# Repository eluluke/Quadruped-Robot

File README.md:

# Quadruped Robot

Open-source, 3D-printable, modular quadruped robot designed as a hardware platform for robotics education, controls development, kinematics, reinforcement learning, robotic vision, and future semi-commercial research applications.

This project focuses on building a practical legged robot platform using custom cycloidal actuators, off-the-shelf electronics, CAN-based motor communication, and open-source low-level motor control software. The goal is to create a robot that is mechanically capable, reproducible, and flexible enough for future work in locomotion, autonomous navigation, and robotics research.

## Project Overview

The quadruped is a 12-degree-of-freedom robotic platform with three actuated joints per leg. The mechanical design uses custom 3D-printed cycloidal actuators with a 17:1 gear ratio. These actuators were designed to make the robot modular, serviceable, and easier to manufacture using accessible tools such as 3D printers.

The CAD design is complete, and the actuator assemblies have been built. The current electronics setup uses off-the-shelf hardware for development and testing, while the repository also includes ongoing custom FOC driver board design files. Software development is focused on low-level actuator communication, calibration, inverse kinematics, single-leg testing, and full quadruped locomotion.

Full walking is still under development.

## Current Status

| Area                          | Status                                                   |
| ----------------------------- | -------------------------------------------------------- |
| CAD design                    | Complete                                                 |
| Actuator design               | Complete                                                 |
| Actuator build                | Complete                                                 |
| Electronics                   | Off-the-shelf electronics currently used for development |
| Custom FOC board              | KiCad design files included / in development             |
| Low-level motor communication | Based on Berkeley Humanoid Lite low-level code           |
| Calibration scripts           | In progress                                              |
| Single-leg control            | In progress                                              |
| Full quadruped walking        | In development                                           |
| Vision/autonomy               | Future work                                              |

## Features

* 12-DOF quadruped layout
* Three actuators per leg
* Custom 17:1 cycloidal actuator design
* 3D-printable mechanical structure
* Modular leg and actuator design
* CAD files for the full robot body, legs, and accessories
* CAN-based actuator communication
* Low-level motor control using Berkeley Humanoid Lite/Recoil-style communication code
* Calibration scripts for actuator setup and configuration
* Forward and inverse kinematics tools
* Early locomotion and gait-control scripts
* Xbox controller testing scripts for manual actuator/robot control
* KiCad files for custom FOC driver board development
* BOM and purchasing documentation

## Repository Structure

```text
Quadruped-Robot/
├── 3D_Model/
│   ├── Accessory/
│   ├── Quadruped Body/
│   └── Quadruped Leg/
│
├── Control_Code/
│   ├── Calibration/
│   ├── Locomotion/
│   ├── lowlevel_actuator/
│   ├── quad_ik_can/
│   └── recoil/
│
├── Documentation/
│
├── KiCAD Files/
│   ├── 3D models/
│   ├── BHL_S1_Current/
│   ├── Footprints/
│   ├── Protoype1_Final_revision/
│   └── Symbols/
│
├── Motor_Firmware/
│
├── Purchasing/
│   ├── BOM/
│   └── RFF/
│
└── README.md
```
CAD files are maintained separately at:
https://github.com/eluluke/Quadruped_Robot_Moo_CAD
## Folder Descriptions

### `3D_Model/`

Contains the mechanical design files for the robot. This includes accessory parts, the quadruped body assembly, and leg assembly files.

Important areas include:

* `Accessory/` — printable accessory parts such as body covers and handles
* `Quadruped Body/` — full robot body assembly files
* `Quadruped Leg/` — leg assembly files

These files are used for manufacturing, assembly planning, and future mechanical revisions.

### `Control_Code/`

Contains the Python control software for actuator testing, calibration, kinematics, and early locomotion development.

#### `Control_Code/Calibration/`

Scripts used for setting up and validating individual actuators and motor controllers.

Examples include:

* `ping.py` — basic communication test
* `calibrate_electrical_offset.py` — motor/encoder electrical offset calibration
* `configure_parameter.py` — motor controller parameter configuration
* `read_configurations.py` — read back motor controller settings
* `move_actuator.py` — basic actuator motion test

#### `Control_Code/Locomotion/`

Main area for robot-level locomotion development.

Includes:

* Forward kinematics
* Inverse kinematics
* Leg configuration
* Gain configuration
* Gait scheduling
* Robot controller scripts
* Xbox controller configuration
* IMU reading utilities
* Single-leg and quadruped testing scripts

Notable files include:

* `quadruped_leg_fk.py`
* `quadruped_leg_ik.py`
* `leg_controller.py`
* `robot_controller.py`
* `gait_scheduler.py`
* `quadruped_main_slim.py`
* `quadruped_main_state.py`
* `single_leg_trot.py`
* `remote_single_leg_trot.py`
* `xbox_home_v5.py`
* `read_bno055_live.py`

#### `Control_Code/lowlevel_actuator/`

Contains lower-level actuator test scripts used to command one or more actuators directly.

Examples include:

* `actuator_move_position.py`
* `actuator_ramp_position.py`
* `actuator_ramp_rel_pos.py`
* `triple_actuator_homing.py`
* `triple_actuator_rel_pos.py`
* `xbox_position_control_test.py`
* `xbox_velocity_control_test.py`

These scripts are useful for validating actuator behavior before integrating the full robot.

#### `Control_Code/quad_ik_can/`

Contains an additional inverse-kinematics-over-CAN control workflow.

Includes:

* `can_interface.py`
* `config.py`
* `ik_solver.py`
* `main.py`
* `README.md`

This section appears to be focused on combining inverse kinematics commands with CAN communication.

#### `Control_Code/recoil/`

Contains the low-level Recoil-style communication code used to interface with the FOC motor drivers.

This project uses the Berkeley Humanoid Lite low-level code as the foundation for communicating with the FOC drivers.

Files include:

* `can.py`
* `core.py`
* `fixed16.py`
* `util.py`

## Mechanical Design

The robot is built around custom cycloidal actuators. Each actuator is designed to be compact, modular, and manufacturable with accessible tools. The use of a cycloidal gearbox provides a high reduction ratio while keeping the actuator package suitable for legged robotics.

The mechanical system was designed with the following goals:

* Keep the robot modular and easy to repair
* Make the actuator design reproducible
* Use 3D printing where practical
* Reduce complexity compared to fully custom machined systems
* Provide enough torque and structure for walking development
* Create a platform that can support future controls and autonomy work

## Electronics

The current robot uses off-the-shelf electronics for development and testing. This makes it easier to focus on actuator validation, CAN communication, calibration, and walking control before depending on fully custom hardware.

The repository also includes KiCad files for custom FOC driver board development. These files include PCB designs, schematics, footprints, symbols, 3D models, and previous design revisions.

### `KiCAD Files/`

This folder contains custom motor controller PCB design files and related KiCad resources.

Included resources:

* KiCad project files
* PCB layout files
* Schematic files
* Footprints
* Symbols
* 3D models
* Older board revisions
* Prototype revisions

This section is useful for future development of custom motor-control electronics.

### `Motor_Firmware/`

Contains motor firmware resources, including a modified Recoil motor controller firmware archive.

## Software

The control software is written primarily in Python and is organized around actuator bring-up, calibration, inverse kinematics, and locomotion development.

The current low-level communication approach is based on the Berkeley Humanoid Lite low-level code. This code is used to communicate with the FOC drivers and send actuator commands over CAN.

### Software Goals

* Establish reliable communication with each actuator
* Test individual motor and actuator behavior
* Validate actuator direction, encoder feedback, and control modes
* Calibrate electrical offsets and controller parameters
* Develop single-leg control
* Develop inverse kinematics for each leg
* Build toward coordinated full-body locomotion
* Eventually support higher-level walking, autonomy, and vision experiments

## Running and Testing

Example test scripts are available in the Berkeley Humanoid Lite low-level software and in this repository’s `Control_Code/` folder.

A typical development workflow is:

1. Set up the Python environment.
2. Connect the CAN interface and motor controller hardware.
3. Confirm communication with the actuator.
4. Run a basic ping or configuration read test.
5. Calibrate the actuator electrical offset.
6. Test basic actuator movement.
7. Test multiple actuators together.
8. Run inverse kinematics tests.
9. Test single-leg motion.
10. Move toward full quadruped locomotion.

Example scripts to start with:

```bash
python Control_Code/Calibration/ping.py
python Control_Code/Calibration/read_configurations.py
python Control_Code/Calibration/calibrate_electrical_offset.py
python Control_Code/Calibration/move_actuator.py
```

For low-level actuator tests:

```bash
python Control_Code/lowlevel_actuator/actuator_move_position.py
python Control_Code/lowlevel_actuator/actuator_ramp_position.py
python Control_Code/lowlevel_actuator/triple_actuator_homing.py
```

For locomotion and kinematics development:

```bash
python Control_Code/Locomotion/ik_terminal_test.py
python Control_Code/Locomotion/single_leg_trot.py
python Control_Code/Locomotion/quadruped_main_slim.py
python Control_Code/Locomotion/quadruped_main_state.py
```

Exact commands may need to be adjusted depending on the CAN interface, operating system, motor IDs, and hardware configuration.

## Development Notes

This project is still actively being developed. Many scripts are experimental and may need to be updated for a specific hardware setup.

Before running full robot tests, verify:

* CAN interface name and bitrate
* Motor controller IDs
* Encoder direction
* Motor phase order
* Joint limits
* Homing offsets
* Control gains
* Power supply current limit
* Emergency stop or disconnect method

## Safety Notes

This project involves motors, gear reductions, motor controllers, power electronics, and moving robotic limbs. Use caution when testing.

Recommended safety practices:

* Test actuators one at a time before full robot integration
* Keep the robot lifted or supported during early walking tests
* Use current limits during initial motor testing
* Keep hands, wires, and tools away from moving joints
* Have an emergency stop or quick power disconnect available
* Double-check wiring before applying power
* Verify motor direction before installing actuators into the full robot
* Confirm joint limits before running autonomous motion
* Avoid testing high-power motion near people or fragile objects
* Monitor motor and driver temperature during testing
* Do not leave powered actuators unattended

This robot is still under development, so all testing should be done carefully and incrementally.

## Documentation

The `Documentation/` folder contains project images and supporting documents. More build documentation, assembly instructions, wiring diagrams, CAD renders, and videos will be added as the project progresses.

## Purchasing and BOM

The `Purchasing/` folder contains bill of materials files, expense tracking, and request-for-funding documentation.

This includes:

* FOC drive board BOM
* Overall robot BOM
* Expense tracker
* Funding/request documentation

These files are useful for tracking cost, sourcing parts, and documenting project funding.

## Roadmap

### Completed

* Designed the full quadruped CAD model
* Designed custom cycloidal actuators
* Built the actuator assemblies
* Created 3D-printable body, leg, and accessory files
* Set up off-the-shelf electronics for development
* Added low-level actuator testing scripts
* Added calibration scripts
* Added forward and inverse kinematics code
* Added early locomotion and single-leg test scripts
* Added KiCad files for custom FOC driver board development

### In Progress

* Low-level actuator testing
* Motor communication and control validation
* Actuator calibration
* Leg-level control development
* Gait scheduling
* Single-leg trot testing
* Full quadruped walking development

### Future Work

* Full quadruped walking demo
* Improved gait generation
* Higher-level body control
* Autonomous navigation
* Robotic vision integration
* Custom electronics refinement
* Cleaner software setup instructions
* Assembly guide
* Wiring diagrams
* CAD renders and demo videos
* More complete documentation for calibration and testing

## Acknowledgments

This project uses the Berkeley Humanoid Lite low-level code as the foundation for communication with the FOC drivers.

The project is inspired by open-source robotics platforms and the goal of making advanced legged robotics more accessible for students, researchers, and builders.

## Project Status Disclaimer

This repository is still a work in progress. The CAD and actuator builds are complete, but full walking control is still under development. Some scripts are experimental and may require hardware-specific configuration before use.

## License

License information has not been finalized yet. Add the appropriate license before using this project for public distribution or commercial work.

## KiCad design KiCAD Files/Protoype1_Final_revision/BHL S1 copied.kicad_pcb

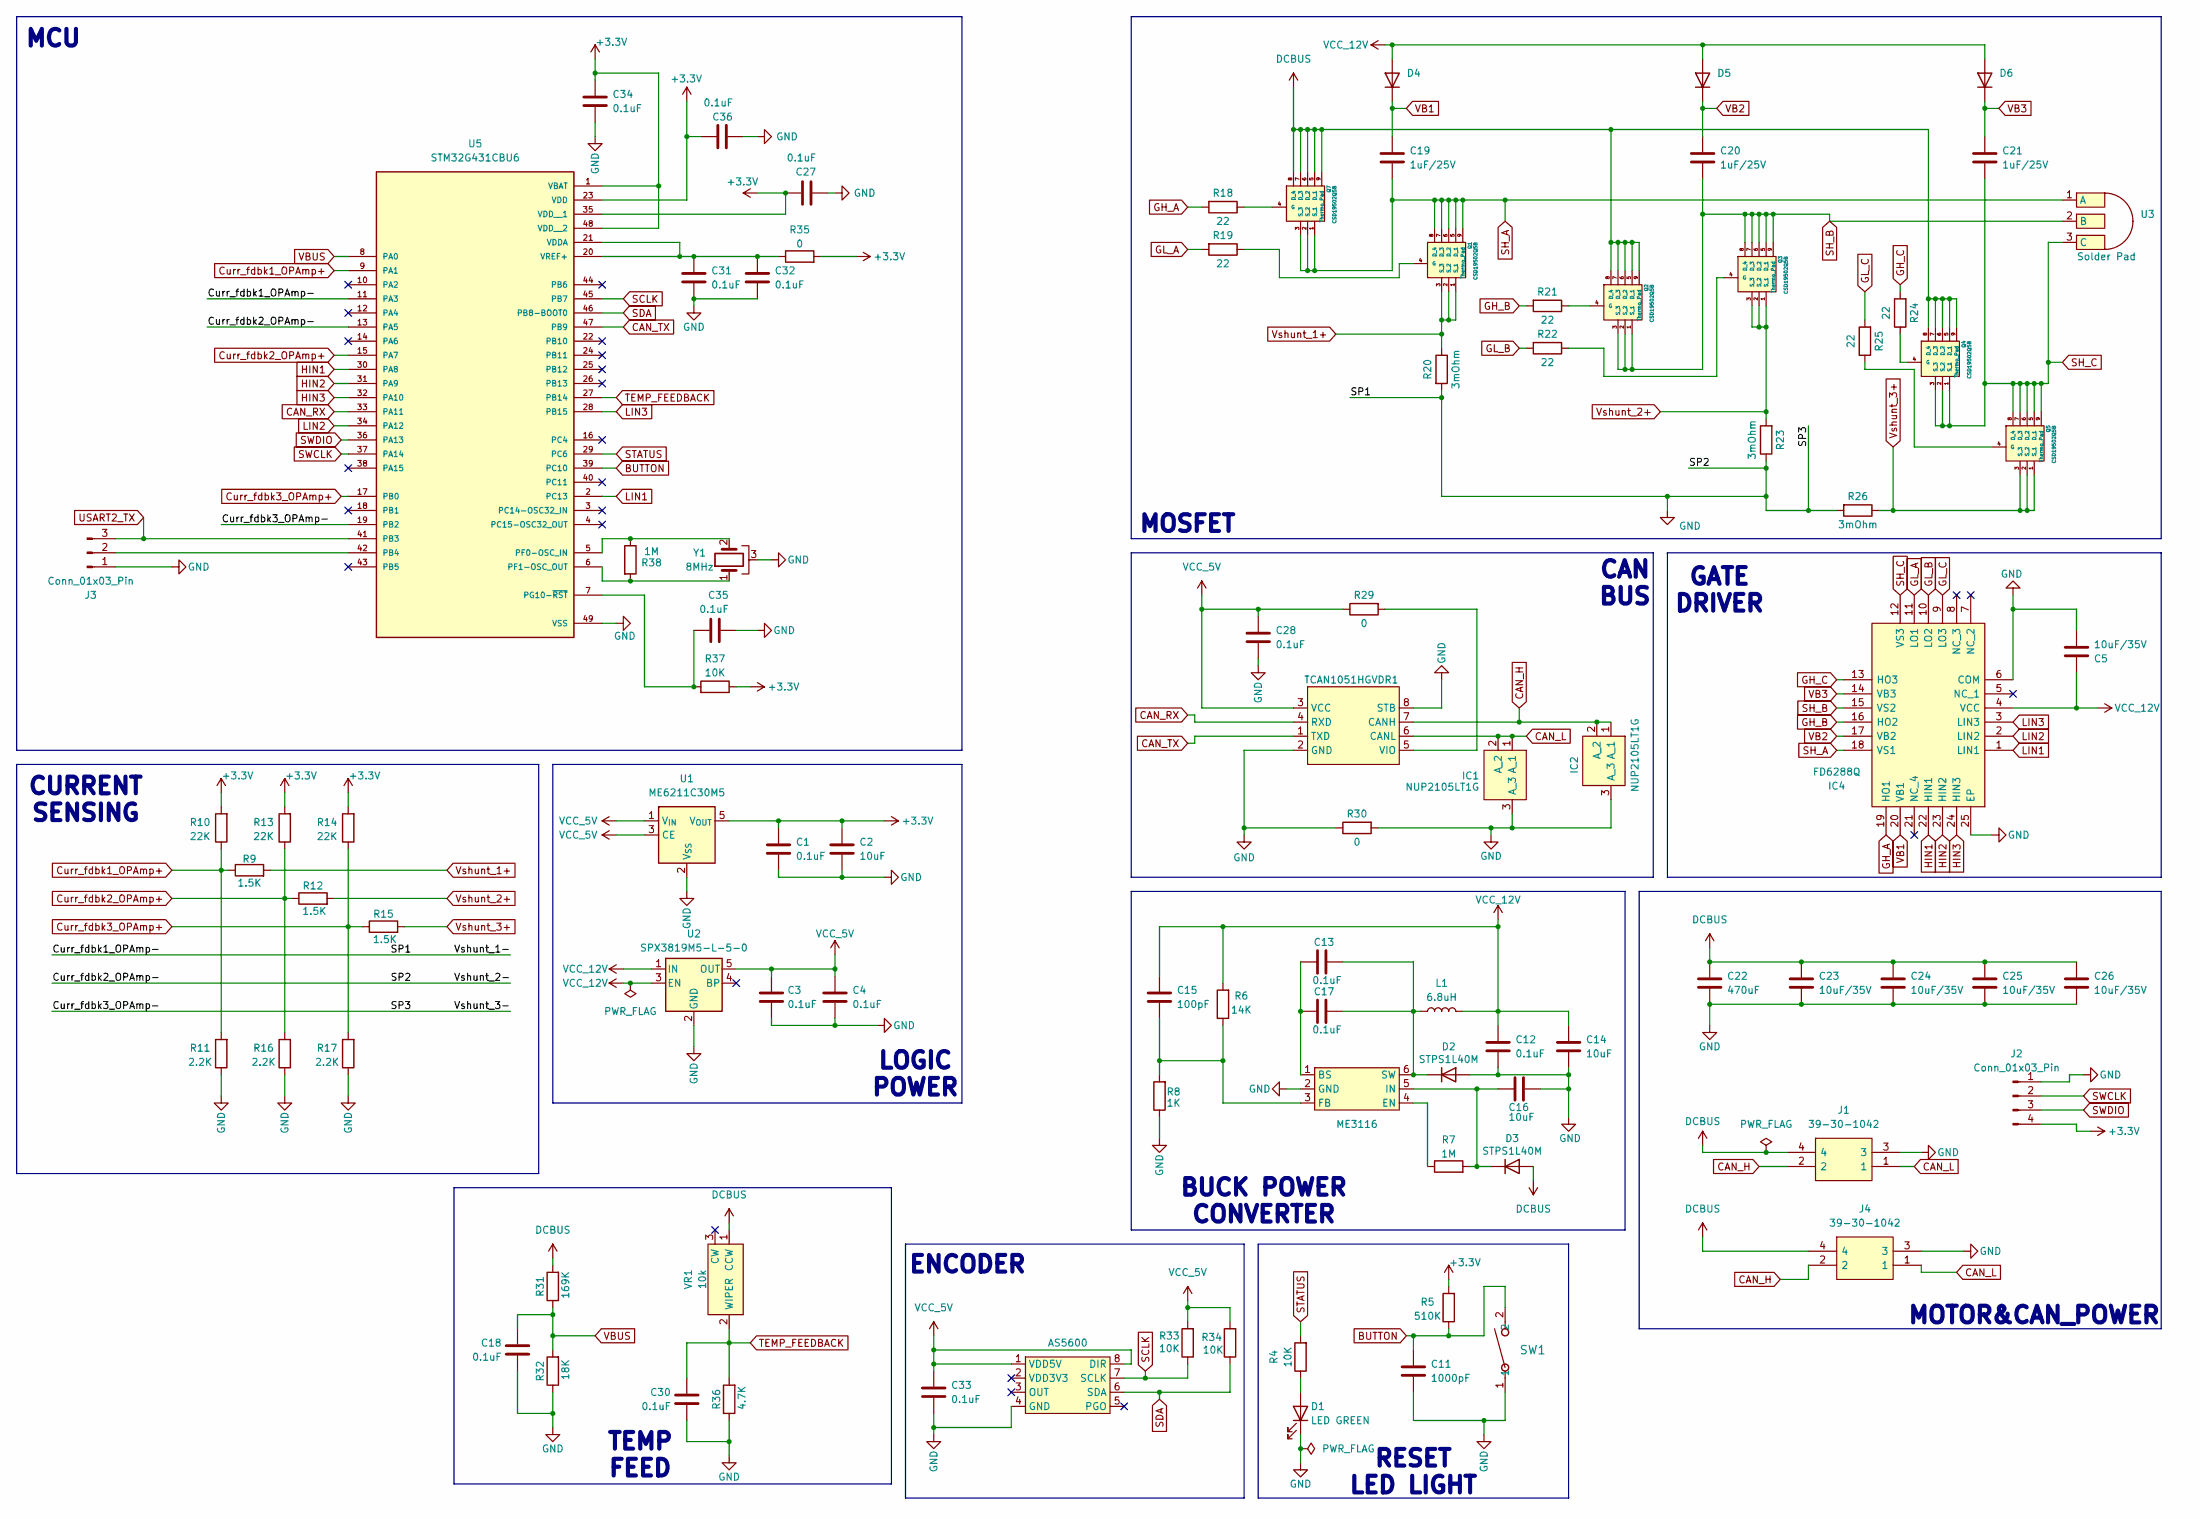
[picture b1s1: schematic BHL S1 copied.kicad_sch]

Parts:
AS5600: AS5600
C1, C3, C4, C12, C13, C17, C18, C27, C28, C30, C31, C32, C33, C34, C35, C36: 0.1uF; C_0402_1005Metric_Pad0.74x0.62mm_HandSolder
C2: 10uF; C_0402_1005Metric_Pad0.74x0.62mm_HandSolder
C5: 10uF/35V; C_0603_1608Metric_Pad1.08x0.95mm_HandSolder
C11: 1000pF; C_0402_1005Metric_Pad0.74x0.62mm_HandSolder
C14, C16: 10uF; C_0805_2012Metric_Pad1.18x1.45mm_HandSolder
C15: 100pF; C_0603_1608Metric_Pad1.08x0.95mm_HandSolder
C19, C20, C21: 1uF/25V; C_0402_1005Metric_Pad0.74x0.62mm_HandSolder
C22: 470uF; 470uF_10mm_Cap
C23, C24, C25, C26: 10uF/35V; C_0805_2012Metric_Pad1.18x1.45mm_HandSolder
D1: LED GREEN; LED_0402_1005Metric_Pad0.77x0.64mm_HandSolder
D2, D3: STPS1L40M; DIO_STPS1L40M
D4, D5, D6: 1N4148WT; D_SOD-523
IC1, IC2: NUP2105LT1G; SOT96P237X111-3N_DIODE; Mouser Part Number 863-NUP2105LT1G
IC4: FD6288Q; QFN50P400X400X90-25N-D_Gatedriver1; Manufacturer_Part_Number FD6288Q
J1, J4: 39-30-1042; Terminator; Mouser Part Number 538-39-30-1042
J2: Conn_01x03_Pin; PinHeader_1x04_P2.54mm_Vertical
J3: Conn_01x03_Pin; PinHeader_1x03_P2.54mm_Vertical
L1: 6.8uH; INDPM5452X300N_Inductor
ME3116: SOT95P270X145-6N_ME3116
Q1, Q2, Q3, Q4, Q5, Q7: CSD19502Q5B; CSD19502Q5B_MOSFET; Mouser Part Number 595-CSD19502Q5B
R4, R37: 10K; R_01005_0402Metric_Pad0.57x0.30mm_HandSolder
R5: 510K; R_01005_0402Metric_Pad0.57x0.30mm_HandSolder
R6: 14K; R_0402_1005Metric_Pad0.72x0.64mm_HandSolder
R7: 1M; R_0603_1608Metric_Pad0.98x0.95mm_HandSolder
R8: 1K; R_0402_1005Metric_Pad0.72x0.64mm_HandSolder
R9, R12, R15: 1.5K; R_0402_1005Metric_Pad0.72x0.64mm_HandSolder
R10, R13, R14: 22K; R_0402_1005Metric_Pad0.72x0.64mm_HandSolder
R11, R16, R17: 2.2K; R_0402_1005Metric_Pad0.72x0.64mm_HandSolder
R18, R19, R21, R22, R24, R25: 22; R_0402_1005Metric_Pad0.72x0.64mm_HandSolder
R20, R23, R26: 3mOhm; R_2512_6332Metric_Pad1.40x3.35mm_HandSolder
R29, R30: 0; R_0402_1005Metric_Pad0.72x0.64mm_HandSolder
R31: 169K; R_0402_1005Metric_Pad0.72x0.64mm_HandSolder
R32: 18K; R_0402_1005Metric_Pad0.72x0.64mm_HandSolder
R33, R34: 10K; R_0402_1005Metric_Pad0.72x0.64mm_HandSolder
R35: 0; R_01005_0402Metric_Pad0.57x0.30mm_HandSolder
R36: 4.7K; R_0402_1005Metric_Pad0.72x0.64mm_HandSolder
R38: 1M; R_0402_1005Metric_Pad0.72x0.64mm_HandSolder
SW1: PTS636 SM50J SMTR LFS; SW_PTS636_CNK
TCAN1051HGVDR1: SOIC127P600X175-8N_CAN
U1: ME6211C30M5; SOT-23-5
U2: SPX3819M5-L-5-0; SOT-23-5
U3: Solder Pad; Soldering Pad for BLDC motor
U5: STM32G431CBU6; QFN50P700X700X60-49N_STM32; PARTREV 6
VR1: 10k; Trimmer_Potentiometer; Mouser Part Number 652-3314J-1-103G
Y1: 8MHz; CSTNE8M00G55Z000R0_Resonator

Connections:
+3.3V: C1.1, C2.1, C27.1, C34.1, C36.1, J2.4, R5.2, R10.2, R13.2, R14.2, R35.2, R37.1, U1.5 (V_{OUT}), U5.1 (VBAT), U5.23 (VDD), U5.35 (VDD__1), U5.48 (VDD__2)
BUTTON: C11.1, R5.1, SW1.2, U5.39 (PC10)
CAN_H: IC2.1 (A), IC2.2 (A), J1.2, J4.2, TCAN1051HGVDR1.7 (CANH)
CAN_L: IC1.1 (A), IC1.2 (A), J1.1, J4.1, TCAN1051HGVDR1.6 (CANL)
CAN_RX: TCAN1051HGVDR1.4 (RXD), U5.33 (PA11)
CAN_TX: TCAN1051HGVDR1.1 (TXD), U5.47 (PB9)
Curr_fdbk1_OPAmp+: R9.1, R10.1, R11.2, U5.9 (PA1)
Curr_fdbk2_OPAmp+: R12.1, R13.1, R16.2, U5.15 (PA7)
Curr_fdbk3_OPAmp+: R14.1, R15.1, R17.2, U5.17 (PB0)
DCBUS: C22.1, C23.1, C24.1, C25.1, C26.1, D3.2 (A), J1.4, J4.4, Q2.5 (D_1), Q2.6 (D_2), Q2.7 (D_3), Q2.8 (D_4), Q2.9 (Thermo_Pad), Q4.5 (D_1), Q4.6 (D_2), Q4.7 (D_3), Q4.8 (D_4), Q4.9 (Thermo_Pad), Q7.5 (D_1), Q7.6 (D_2), Q7.7 (D_3), Q7.8 (D_4), Q7.9 (Thermo_Pad), R31.2, VR1.1 (CCW)
GH_A: IC4.19 (HO1), R18.2
GH_B: IC4.16 (HO2), R21.2
GH_C: IC4.13 (HO3), R24.2
GL_A: IC4.11 (LO1), R19.2
GL_B: IC4.10 (LO2), R22.2
GL_C: IC4.9 (LO3), R25.2
GND: AS5600.4 (GND), C1.2, C2.2, C3.2, C4.2, C5.2, C11.2, C12.2, C14.2, C16.1, C18.2, C22.2, C23.2, C24.2, C25.2, C26.2, C27.2, C28.2, C30.2, C31.2, C32.2, C33.2, C34.2, C35.1, C36.2, D1.1 (K), D2.2 (A), IC1.3 (A), IC2.3 (A), IC4.6 (COM), IC4.25 (EP), J1.3, J2.1, J3.1, J4.3, ME3116.2 (GND), R8.1, R11.1, R16.1, R17.1, R20.2, R23.1, R26.2, R30.1, R30.2, R32.1, R36.1, SW1.1, TCAN1051HGVDR1.2 (GND), TCAN1051HGVDR1.8 (STB), U1.2 (V_{SS}), U2.2 (GND), U5.11 (PA3), U5.13 (PA5), U5.19 (PB2), U5.49 (VSS), Y1.3
HIN1: IC4.22 (HIN1), U5.30 (PA8)
HIN2: IC4.23 (HIN2), U5.31 (PA9)
HIN3: IC4.24 (HIN3), U5.32 (PA10)
LIN1: IC4.1 (LIN1), U5.2 (PC13)
LIN2: IC4.2 (LIN2), U5.34 (PA12)
LIN3: IC4.3 (LIN3), U5.28 (PB15)
unnamed: D1.2 (A), R4.1
unnamed: C13.2, C17.2, D2.1 (K), L1.1, ME3116.6 (SW)
unnamed: C16.2, D3.1 (K), ME3116.5 (IN), R7.2
unnamed: J3.2, U5.42 (PB4)
unnamed: C13.1, C17.1, ME3116.1 (BS)
unnamed: ME3116.4 (EN), R7.1
unnamed: C15.2, ME3116.3 (FB), R6.1, R8.2
unnamed: Q1.4 (G), R19.1
unnamed: Q2.4 (G), R21.1
unnamed: Q3.4 (G), R22.1
unnamed: Q4.4 (G), R24.1
unnamed: Q5.4 (G), R25.1
unnamed: Q7.4 (G), R18.1
unnamed: R29.2, TCAN1051HGVDR1.5 (VIO)
unnamed: R38.1, U5.5 (PF0-OSC_IN), Y1.2
unnamed: R38.2, U5.6 (PF1-OSC_OUT), Y1.1
unnamed: C35.2, R37.2, U5.7 (PG10-~RST)
unnamed: C31.1, C32.1, R35.1, U5.20 (VREF+), U5.21 (VDDA)
SCLK: AS5600.7 (SCLK), R33.1, U5.45 (PB7)
SDA: AS5600.6 (SDA), R34.1, U5.46 (PB8-BOOT0)
SH_A: C19.2, IC4.18 (VS1), Q1.5 (D_1), Q1.6 (D_2), Q1.7 (D_3), Q1.8 (D_4), Q1.9 (Thermo_Pad), Q7.1 (S_1), Q7.2 (S_2), Q7.3 (S_3), U3.1 (A)
SH_B: C20.2, IC4.15 (VS2), Q2.1 (S_1), Q2.2 (S_2), Q2.3 (S_3), Q3.5 (D_1), Q3.6 (D_2), Q3.7 (D_3), Q3.8 (D_4), Q3.9 (Thermo_Pad), U3.2 (B)
SH_C: C21.2, IC4.12 (VS3), Q4.1 (S_1), Q4.2 (S_2), Q4.3 (S_3), Q5.5 (D_1), Q5.6 (D_2), Q5.7 (D_3), Q5.8 (D_4), Q5.9 (Thermo_Pad), U3.3 (C)
STATUS: R4.2, U5.29 (PC6)
SWCLK: J2.2, U5.37 (PA14)
SWDIO: J2.3, U5.36 (PA13)
TEMP_FEEDBACK: C30.1, R36.2, U5.27 (PB14), VR1.2 (WIPER)
USART2_TX: J3.3, U5.41 (PB3)
VB1: C19.1, D4.1 (K), IC4.20 (VB1)
VB2: C20.1, D5.1 (K), IC4.17 (VB2)
VB3: C21.1, D6.1 (K), IC4.14 (VB3)
VBUS: C18.1, R31.1, R32.2, U5.8 (PA0)
VCC_5V: AS5600.1 (VDD5V), AS5600.8 (DIR), C3.1, C4.1, C28.1, C33.1, R29.1, R33.2, R34.2, TCAN1051HGVDR1.3 (VCC), U1.1 (V_{IN}), U1.3 (CE), U2.5 (OUT)
VCC_12V: C5.1, C12.1, C14.1, C15.1, D4.2 (A), D5.2 (A), D6.2 (A), IC4.4 (VCC), L1.2, R6.2, U2.1 (IN), U2.3 (EN)
Vshunt_1+: Q1.1 (S_1), Q1.2 (S_2), Q1.3 (S_3), R9.2, R20.1
Vshunt_2+: Q3.1 (S_1), Q3.2 (S_2), Q3.3 (S_3), R12.2, R23.2
Vshunt_3+: Q5.1 (S_1), Q5.2 (S_2), Q5.3 (S_3), R15.2, R26.1

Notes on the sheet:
ENCODER
RESET LED LIGHT
MOSFET
TEMP FEED
MCU
BUCK POWER CONVERTER
LOGIC POWER
CURRENT SENSING
GATE DRIVER
MOTOR&CAN_POWER
CAN BUS

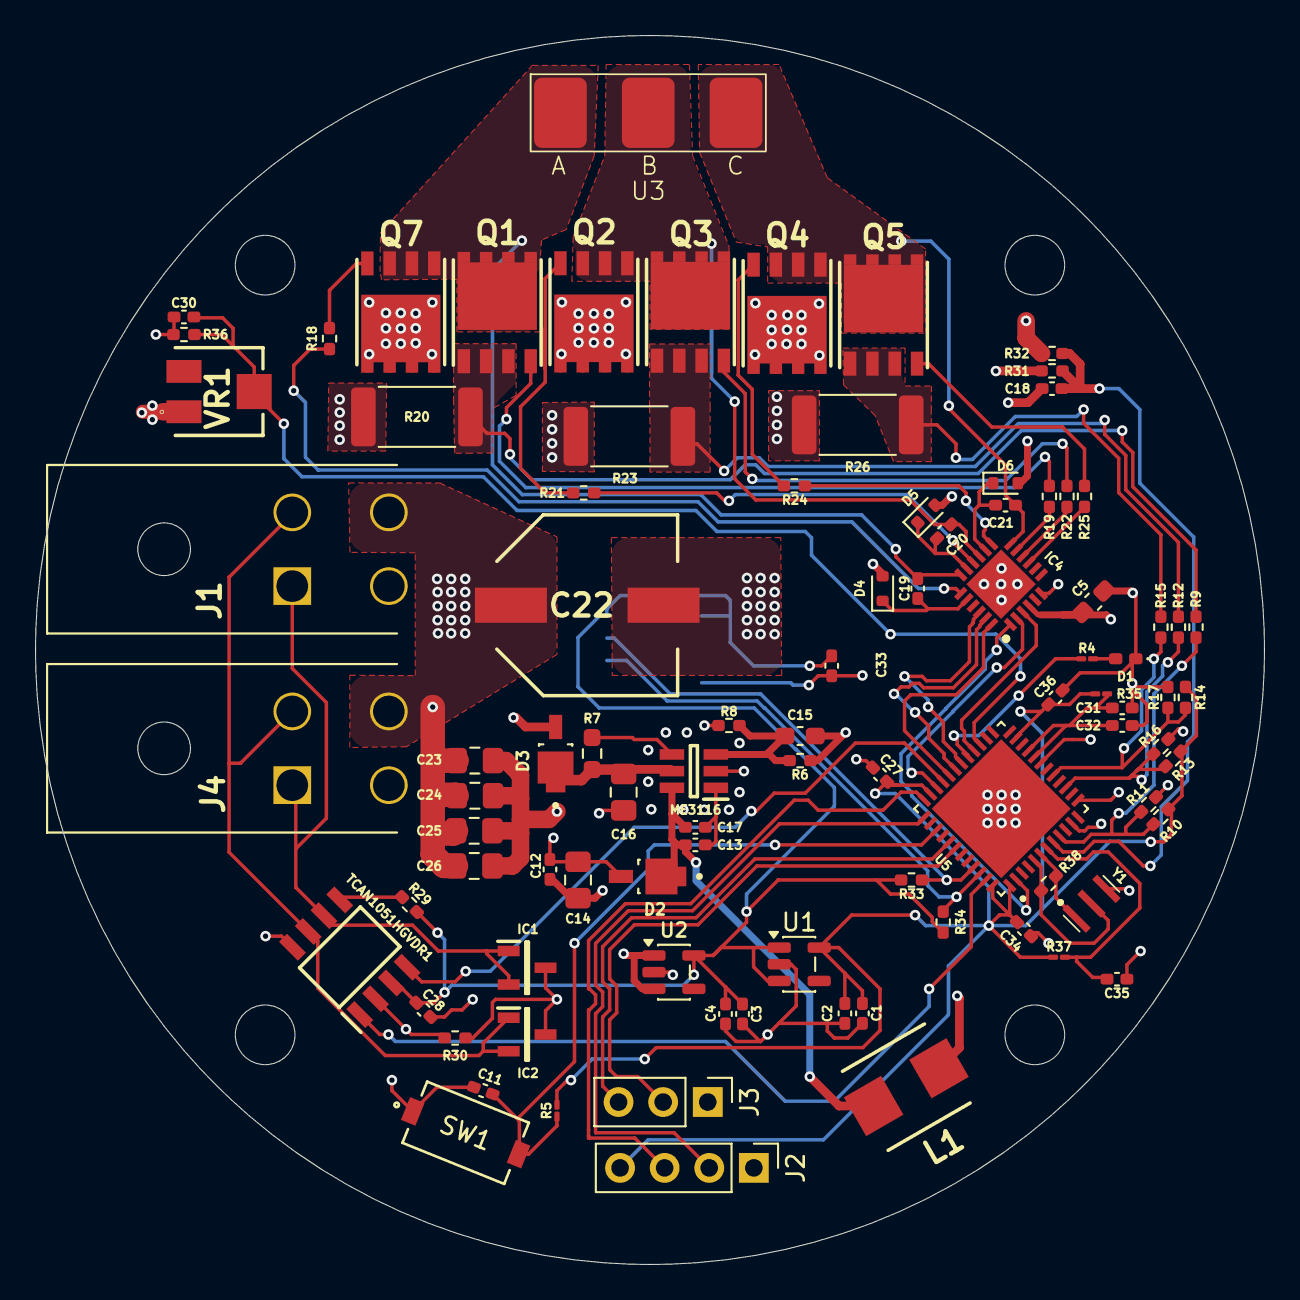
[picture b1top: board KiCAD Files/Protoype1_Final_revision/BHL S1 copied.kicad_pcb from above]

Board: 4 copper layers, 70.0 x 70.0 mm, 93 parts (1 on the bottom side), 60 nets.

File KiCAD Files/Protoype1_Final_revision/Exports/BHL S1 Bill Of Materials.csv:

"Id";"Designator";"Footprint";"Quantity";"Designation";"Supplier and ref";
1;"C27,C35,C18,C1,C34,C4,C12,C31,C33,C28,C32,C30,C3,C17,C13,C36";"C_0402_1005Metric_Pad0.74x0.62mm_HandSolder";16;"0.1uF";;;
2;"C23,C25,C24,C26";"C_0805_2012Metric_Pad1.18x1.45mm_HandSolder";4;"10uF/35V";;;
3;"R21,R24,R19,R22,R25,R18";"R_0402_1005Metric_Pad0.72x0.64mm_HandSolder";6;"22";;;
4;"R38";"R_0402_1005Metric_Pad0.72x0.64mm_HandSolder";1;"1M";;;
5;"C11";"C_0402_1005Metric_Pad0.74x0.62mm_HandSolder";1;"1000pF";;;
6;"R20,R23,R26";"R_1206_3216Metric_Pad1.30x1.75mm_HandSolder";3;"3mOhm";;;
7;"C22";"470uF_10mm_Cap";1;"470uF";;;
8;"R12,R9,R15";"R_0402_1005Metric_Pad0.72x0.64mm_HandSolder";3;"1.5K";;;
9;"D5,D4,D6";"D_SOD-523";3;"1N4148WT";;;
10;"J2,J3";"PinHeader_1x03_P2.54mm_Vertical";2;"Conn_01x03_Pin";;;
11;"L1";"INDPM5452X300N_Inductor";1;"6.8uH";;;
12;"ME3116";"SOT95P270X145-6N_ME3116";1;"~";;;
13;"U1";"SOT-23-5";1;"ME6211C30M5";;;
14;"IC2,IC1";"SOT96P237X111-3N_DIODE";2;"NUP2105LT1G";;;
15;"R29,R30";"R_0402_1005Metric_Pad0.72x0.64mm_HandSolder";2;"0";;;
16;"Q5,Q2,Q1,Q7,Q3,Q4";"CSD19502Q5B_MOSFET";6;"CSD19502Q5B";;;
17;"R35";"R_01005_0402Metric_Pad0.57x0.30mm_HandSolder";1;"0";;;
18;"D1";"LED_0402_1005Metric_Pad0.77x0.64mm_HandSolder";1;"LED GREEN";;;
19;"IC4";"QFN50P400X400X90-25N-D_Gatedriver1";1;"FD6288Q";;;
20;"R13,R14,R10";"R_0402_1005Metric_Pad0.72x0.64mm_HandSolder";3;"22K";;;
21;"R8";"R_0402_1005Metric_Pad0.72x0.64mm_HandSolder";1;"1K";;;
22;"D2,D3";"D_SOD-523";2;"STPS1L40M";;;
23;"R31";"R_0402_1005Metric_Pad0.72x0.64mm_HandSolder";1;"169K";;;
24;"R37,R4";"R_01005_0402Metric_Pad0.57x0.30mm_HandSolder";2;"10K";;;
25;"J1,J4";"Terminator";2;"39-30-1042";;;
26;"C21,C19,C20";"C_0402_1005Metric_Pad0.74x0.62mm_HandSolder";3;"1uF/25V";;;
27;"R16,R11,R17";"R_0402_1005Metric_Pad0.72x0.64mm_HandSolder";3;"2.2K";;;
28;"C16,C14";"C_0805_2012Metric_Pad1.18x1.45mm_HandSolder";2;"10uF";;;
29;"U2";"SOT-23-5";1;"SPX3819M5-L-5-0";;;
30;"R5";"R_01005_0402Metric_Pad0.57x0.30mm_HandSolder";1;"510K";;;
31;"R34,R33";"R_0402_1005Metric_Pad0.72x0.64mm_HandSolder";2;"10K";;;
32;"SW1";"SW_PTS636_CNK";1;"PTS636 SM50J SMTR LFS";;;
33;"U5";"QFN50P700X700X60-49N_STM32";1;"STM32G431CBU6";;;
34;"R36";"R_0402_1005Metric_Pad0.72x0.64mm_HandSolder";1;"4.7K";;;
35;"TCAN1051HGVDR1";"SOIC127P600X175-8N_CAN";1;"~";;;
36;"VR1";"Trimmer_Potentiometer";1;"10k";;;
37;"C5";"C_0603_1608Metric_Pad1.08x0.95mm_HandSolder";1;"10uF/35V";;;
38;"C2";"C_0402_1005Metric_Pad0.74x0.62mm_HandSolder";1;"10uF";;;
39;"R32";"R_0402_1005Metric_Pad0.72x0.64mm_HandSolder";1;"18K";;;
40;"C15";"C_0603_1608Metric_Pad1.08x0.95mm_HandSolder";1;"100pF";;;
41;"U3";"Soldering Pad for BLDC motor";1;"Solder Pad";;;
42;"Y1";"CSTNE8M00G55Z000R0_Resonator";1;"8MHz";;;
43;"R7";"R_0603_1608Metric_Pad0.98x0.95mm_HandSolder";1;"1M";;;
44;"R6";"R_0402_1005Metric_Pad0.72x0.64mm_HandSolder";1;"14K";;;
45;"AS5600";"AS5600";1;"~";;;

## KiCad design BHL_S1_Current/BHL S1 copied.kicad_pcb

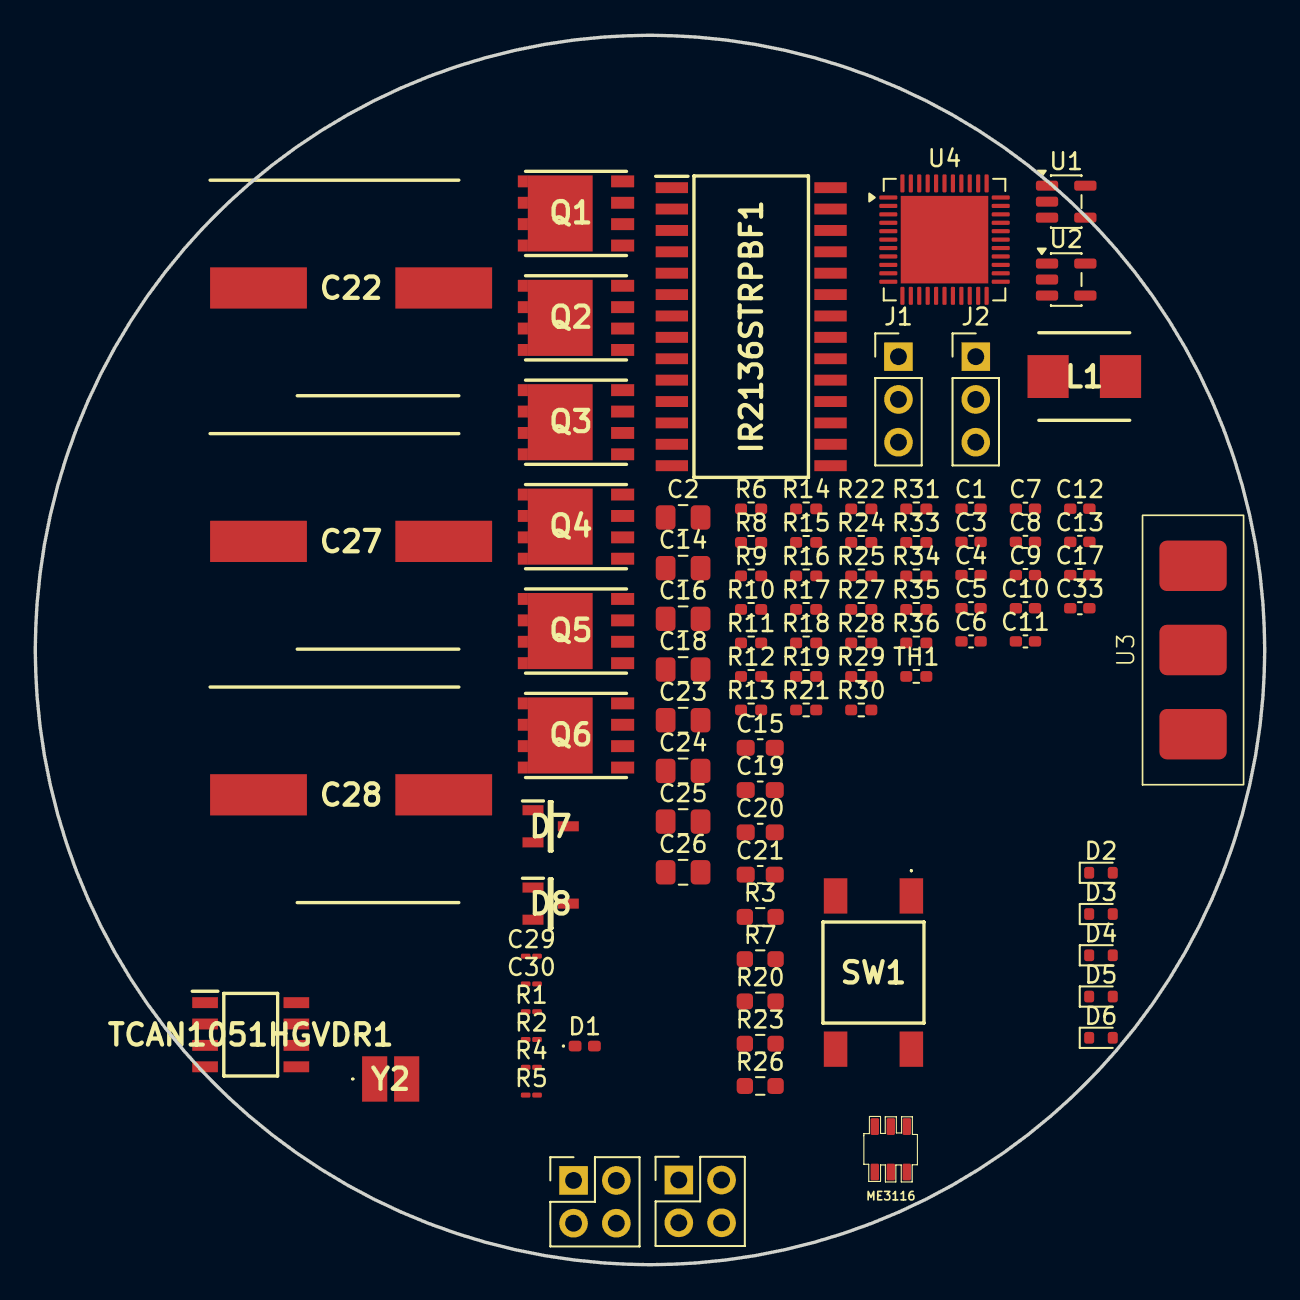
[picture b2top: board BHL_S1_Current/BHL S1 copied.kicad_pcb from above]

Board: 2 copper layers, 73.0 x 73.0 mm, 96 parts (1 on the bottom side), 61 nets, no tracks yet.

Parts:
AS5600: AS5600
C1, C3, C4, C5, C6, C7, C8, C9, C10, C12, C13, C17, C33: 0.1uF; C_0402_1005Metric_Pad0.74x0.62mm_HandSolder
C2, C14, C16: 10uF; C_0805_2012Metric_Pad1.18x1.45mm_HandSolder
C11: 1000pF; C_0402_1005Metric_Pad0.74x0.62mm_HandSolder
C15: 100pF; C_0603_1608Metric_Pad1.08x0.95mm_HandSolder
C18, C23, C24, C25, C26: 10uF/35V; C_0805_2012Metric_Pad1.18x1.45mm_HandSolder
C19, C20, C21: 1uF/25V; C_0603_1608Metric_Pad1.08x0.95mm_HandSolder
C22, C27, C28: 470uF; CAPAE1280X1400N_Electrolytic Capacitor
C29, C30: 0.1uF; C_01005_0402Metric_Pad0.57x0.30mm_HandSolder
D1: LED GREEN; LED_0402_1005Metric_Pad0.77x0.64mm_HandSolder
D2, D3: STPS1L40M; D_SOD-523
D4, D5, D6: 1N4148WT; D_SOD-523
D7, D8: NUP2105; SOT96P237X111-3N_DIODE
Header2X2H1, Header2X2H2: PinHeader_2x02_P2.54mm_Vertical
IR2136STRPBF1: 3PHASE_GATE_DRIVER
J1, J2: Conn_01x03_Pin; PinHeader_1x03_P2.54mm_Vertical
L1: 6.8uH; INDPM5452X300N_Inductor
ME3116: ME3116AM6G_Regulator
Q1, Q2, Q3, Q4, Q5, Q6: CSD19502Q5B; CSD19502Q5B_MOSFET
R1: 0; R_01005_0402Metric_Pad0.57x0.30mm_HandSolder
R2: 10K; R_01005_0402Metric_Pad0.57x0.30mm_HandSolder
R3, R7: 1M; R_0603_1608Metric_Pad0.98x0.95mm_HandSolder
R4, R5: 510; R_01005_0402Metric_Pad0.57x0.30mm_HandSolder
R6: 14K; R_0402_1005Metric_Pad0.72x0.64mm_HandSolder
R8: 1K; R_0402_1005Metric_Pad0.72x0.64mm_HandSolder
R9, R12, R15: 1.5K; R_0402_1005Metric_Pad0.72x0.64mm_HandSolder
R10, R13, R14: 22K; R_0402_1005Metric_Pad0.72x0.64mm_HandSolder
R11, R16, R17: 2.2K; R_0402_1005Metric_Pad0.72x0.64mm_HandSolder
R18, R19, R21, R22, R24, R25: 22; R_0402_1005Metric_Pad0.72x0.64mm_HandSolder
R20, R23, R26: 3mOhm; R_0603_1608Metric_Pad0.98x0.95mm_HandSolder
R27, R28, R29, R30: 0; R_0402_1005Metric_Pad0.72x0.64mm_HandSolder
R31: 169K; R_0402_1005Metric_Pad0.72x0.64mm_HandSolder
R33, R34: 10K; R_0402_1005Metric_Pad0.72x0.64mm_HandSolder
R35: 18K; R_0402_1005Metric_Pad0.72x0.64mm_HandSolder
R36: 4.7K; R_0402_1005Metric_Pad0.72x0.64mm_HandSolder
SW1: SW_Push; Push Button 6x6mm
TCAN1051HGVDR1: SOIC127P600X175-8N_CAN
TH1: 10K; R_0402_1005Metric_Pad0.72x0.64mm_HandSolder
U1: ME6211C30M5; SOT-23-5
U2: SPX3819M5-L-5-0; SOT-23-5
U3: Solder Pad; Soldering Pad for BLDC motor
U4: STM32G431CBUx; QFN-44-1EP_7x7mm_P0.5mm_EP5.2x5.2mm
Y2: 8MHz; ABM8AAIG8000MHzV2RT3_Crystal

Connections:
+3.3V: AS5600.1 (VDD5V), AS5600.8 (DIR), C1.1, C2.1, C3.1, C4.1, C5.1, C6.1, C9.1, C28.1, C33.1, R1.2, R2.1, R5.2, R10.2, R13.2, R14.2, R29.1, R33.2, R34.2, TCAN1051HGVDR1.3 (VCC), TH1.1, U1.1 (V_{IN}), U1.3 (CE), U1.5 (V_{OUT}), U2.5 (OUT), U4.1 (VBAT), U4.23 (VDD), U4.35 (VDD)
BEMF3: U4.16 (PC4), U4.24 (PB11)
BUTTON: C11.1, R5.1, SW1.1, U4.39 (PC10)
CAN_GND: D7.2 (A), D8.2 (A), R30.2, TCAN1051HGVDR1.8 (STB)
CAN_H: D8.1 (K), Header2X2H1.3, Header2X2H2.3, TCAN1051HGVDR1.7 (CANH)
CAN_L: D7.1 (K), Header2X2H1.4, Header2X2H2.4, TCAN1051HGVDR1.6 (CANL)
CAN_RX: TCAN1051HGVDR1.4 (RXD), U4.33 (PA11)
Curr_fdbk1_OPAmp+: R9.1, R10.1, R11.2, U4.9 (PA1)
Curr_fdbk1_OPAmp-: C22.2, C23.2, C24.2, C25.2, C26.2, C27.2, Header2X2H1.2, Header2X2H2.2, R20.2, R23.2, R26.2, R27.1, U4.11 (PA3), U4.13 (PA5), U4.19 (PB2)
Curr_fdbk2_OPAmp+: R12.1, R13.1, R16.2, U4.15 (PA7)
Curr_fdbk3_OPAmp+: R14.1, R15.1, R17.2, U4.17 (PB0)
DCBUS: C22.1, C23.1, C24.1, C25.1, C26.1, C27.1, D3.2 (A), Header2X2H1.1, Header2X2H2.1, Q2.1 (D), Q4.1 (D), Q6.1 (D), R31.1
GH_A: IR2136STRPBF1.19 (H01), R18.2
GH_B: IR2136STRPBF1.16 (HO2), R21.2
GH_C: IR2136STRPBF1.13 (HO3), R24.2
GL_A: IR2136STRPBF1.11 (L01), R19.2
GL_B: IR2136STRPBF1.10 (L02), R22.2
GL_C: IR2136STRPBF1.9 (L03), R25.2
GND: AS5600.4 (GND), C1.2, C2.2, C3.2, C4.2, C5.2, C6.2, C7.2, C8.2, C9.2, C10.1, C11.2, C12.2, C14.2, C16.1, C18.2, C28.2, C29.2, C30.2, C33.2, D1.1 (K), D2.2 (A), IR2136STRPBF1.6 (COM), IR2136STRPBF1.25 (EP), J1.2, J2.2, ME3116.2 (GND), R8.1, R11.1, R16.1, R17.1, R27.2, R28.1, R30.1, R35.2, R36.2, SW1.2, TCAN1051HGVDR1.2 (GND), U1.2 (V_{SS}), U2.2 (GND)
unnamed: D1.2 (A), R4.1
unnamed: C13.2, C17.2, D2.1 (K), L1.1, ME3116.4 (SW)
unnamed: C16.2, D3.1 (K), ME3116.5 (IN), R7.2
unnamed: J1.1, U4.42 (PB4)
unnamed: C13.1, C17.1, ME3116.1 (BS)
unnamed: ME3116.6 (EN), R7.1
unnamed: C15.2, ME3116.3 (FB), R6.1, R8.2
unnamed: Q1.2 (G), R19.1
unnamed: Q2.2 (G), R21.1
unnamed: Q3.2 (G), R22.1
unnamed: Q4.2 (G), R24.1
unnamed: Q5.2 (G), R25.1
unnamed: Q6.2 (G), R18.1
unnamed: R3.2, U4.5 (PF0), Y2.1
unnamed: R3.1, U4.6 (PF1), Y2.2
unnamed: C10.2, R2.2, U4.7 (PG10)
unnamed: C7.1, C8.1, R1.1, U4.20 (VREF+), U4.21 (VDDA)
SCLK: AS5600.7 (SCLK), R33.1
SDA: AS5600.6 (SDA), R34.1, U4.45 (PB7)
SH_A: C19.2, IR2136STRPBF1.18 (VS1), Q1.1 (D), Q6.3 (S), U3.1 (A)
SH_B: C20.2, IR2136STRPBF1.15 (VS2), Q2.3 (S), Q3.1 (D), U3.2 (B)
SH_C: C21.2, IR2136STRPBF1.12 (VS3), Q4.3 (S), Q5.1 (D), U3.3 (C)
STATUS: R4.2, U4.29 (PC6)
SWCLK: J2.1, U4.37 (PA14)
SWDIO: J2.3, U4.36 (PA13)
TEMP_FEEDBACK: C30.1, R36.1, TH1.2, U4.27 (PB14)
TIM1_CH1: IR2136STRPBF1.22 (HN1), U4.30 (PA8)
TIM1_CH1N: IR2136STRPBF1.1 (LIN1), U4.2 (PC13)
TIM1_CH2: IR2136STRPBF1.23 (HN2), U4.31 (PA9)
TIM1_CH2N: IR2136STRPBF1.2 (LIN2), U4.34 (PA12)
TIM1_CH3: IR2136STRPBF1.24 (HN3), U4.32 (PA10)
TIM1_CH3N: IR2136STRPBF1.3 (LIN3), U4.28 (PB15)
USART2_TX: J1.3, U4.41 (PB3)
VB1: C19.1, D4.1 (K), IR2136STRPBF1.20 (VB1)
VB2: C20.1, D5.1 (K), IR2136STRPBF1.17 (VB2)
VB3: C21.1, D6.1 (K), IR2136STRPBF1.14 (VB3)
VBUS: C29.1, R31.2, R35.1, U4.8 (PA0)
VCC_5V_CAN: R29.2, TCAN1051HGVDR1.5 (VIO)
VCC_12V: C12.1, C14.1, C15.1, C18.1, D4.2 (A), D5.2 (A), D6.2 (A), IR2136STRPBF1.4 (VCC), L1.2, R6.2, U2.1 (IN), U2.3 (EN)
Vshunt_1+: Q1.3 (S), R9.2, R20.1
Vshunt_2+: Q3.3 (S), R12.2, R15.2, R23.1
Vshunt_3+: Q5.3 (S), R26.1

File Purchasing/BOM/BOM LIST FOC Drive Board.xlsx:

| Id | Designator | Footprint | Quantity | Designation | Total Bought | Total For 12 Boards | Percentage | 5 Boards | Store Bought | Bought?
 | 1 | C27,C35,C18,C34,C4,C12,C31,C33,C28,C32,C30,C3,C17,C13,C36 | C_0402_1005Metric_Pad0.74x0.62mm_HandSolder | 15 | 0.1uF | 180 | 180 | 1 | 75 | Mouser | X
 | 2 | C23,C25,C24,C26 | C_0805_2012Metric_Pad1.18x1.45mm_HandSolder | 4 | 10uF/35V | 48 | 48 | 1 | 20 | Mouser | X
 | 3 | R21,R24,R19,R22,R25,R18 | R_0402_1005Metric_Pad0.72x0.64mm_HandSolder | 6 | 22 | 72 | 72 | 1 | 30 | Mouser | X
 | 4 | R38 | R_0402_1005Metric_Pad0.72x0.64mm_HandSolder | 1 | 1M | 12 | 12 | 1 | 5 | Mouser | X
 | 5 | C11 | C_0402_1005Metric_Pad0.74x0.62mm_HandSolder | 1 | 1000pF | 12 | 12 | 1 | 5 | Mouser | X
 | 6 | R20,R23,R26 | R_2512_6332Metric_Pad1.40x3.35mm_HandSolder | 3 | 3mOhm | 36 | 36 | 1 | 15 | Mouser | X
 | 7 | C22 | 470uF_10mm_Cap | 1 | 470uF | 12 | 12 | 1 | 5 | Mouser | X
 | 8 | R12,R9,R15 | R_0402_1005Metric_Pad0.72x0.64mm_HandSolder | 3 | 1.5K | 36 | 36 | 1 | 15 | Mouser | X
 | 9 | D5,D4,D6 | D_SOD-523 | 3 | 1N4148WT | 36 | 36 | 1 | 15 | Mouser | X
 | 10 | J2,J3 | PinHeader_1x03_P2.54mm_Vertical | 2 | Conn_01x03_Pin | 24 | 24 | 1 | 10 | Mouser | X
 | 11 | L1 | INDPM5452X300N_Inductor | 1 | 6.8uH | 12 | 12 | 1 | 5 | Mouser | X
 | 12 | ME3116 | SOT95P270X145-6N_ME3116 | 1 | ME3116 | 10 | 12 | 0.83333333333333337 | 5 | MooMoo bought it | X
 | 13 | U1 | SOT-23-5 | 1 | ME6211C30M5 | 10 | 12 | 0.83333333333333337 | 5 | MooMoo bought it | X
 | 14 | IC2,IC1 | SOT96P237X111-3N_DIODE | 2 | NUP2105LT1G | 24 | 24 | 1 | 10 | Mouser | X
 | 15 | R29,R30 | R_0402_1005Metric_Pad0.72x0.64mm_HandSolder | 2 | 0 | 24 | 24 | 1 | 10 | Mouser | X
 | 16 | Q5,Q2,Q1,Q7,Q3,Q4 | CSD19502Q5B_MOSFET | 6 | CSD19502Q5B | 30 | 72 | 0.41666666666666669 | 30 | Mouser | X
 | 17 | R35 | R_01005_0402Metric_Pad0.57x0.30mm_HandSolder | 1 | 0 | 12 | 12 | 1 | 5 | Mouser | X
 | 18 | D1 | LED_0402_1005Metric_Pad0.77x0.64mm_HandSolder | 1 | LED GREEN | 12 | 12 | 1 | 5 | Mouser | X
 | 19 | IC4 | QFN50P400X400X90-25N-D_Gatedriver1 | 1 | FD6288Q | 12 | 12 | 1 | 5 | MooMoo bought it | X
 | 20 | R13,R14,R10 | R_0402_1005Metric_Pad0.72x0.64mm_HandSolder | 3 | 22K | 36 | 36 | 1 | 15 | Mouser | X
 | 21 | R8 | R_0402_1005Metric_Pad0.72x0.64mm_HandSolder | 1 | 1K | 12 | 12 | 1 | 5 | Mouser | X
 | 22 | D2,D3 | D_SOD-523 | 2 | STPS1L40M | 24 | 24 | 1 | 10 | Mouser | X
 | 23 | R31 | R_0402_1005Metric_Pad0.72x0.64mm_HandSolder | 1 | 169K | 12 | 12 | 1 | 5 | Mouser | X
 | 24 | R37,R4 | R_01005_0402Metric_Pad0.57x0.30mm_HandSolder | 2 | 10K | 24 | 24 | 1 | 10 | Mouser | X
 | 25 | J1,J4 | Terminator | 2 | 39-30-1042 | 5 | 24 | 0.20833333333333334 | 10 | Mouser | X
 | 26 | C21,C19,C20 | C_0402_1005Metric_Pad0.74x0.62mm_HandSolder | 3 | 1uF/25V | 36 | 36 | 1 | 15 | Mouser | X
 | 27 | R16,R11,R17 | R_0402_1005Metric_Pad0.72x0.64mm_HandSolder | 3 | 2.2K | 36 | 36 | 1 | 15 | Mouser | X
 | 28 | C16,C14 | C_0805_2012Metric_Pad1.18x1.45mm_HandSolder | 2 | 10uF | 24 | 24 | 1 | 10 | Mouser | X
 | 29 | U2 | SOT-23-5 | 1 | SPX3819M5-L-5-0 | 10 | 12 | 0.83333333333333337 | 5 | MooMoo bought it | X
 | 30 | R5 | R_01005_0402Metric_Pad0.57x0.30mm_HandSolder | 1 | 510K | 12 | 12 | 1 | 5 | DigiKey | X
 | 31 | R34,R33 | R_0402_1005Metric_Pad0.72x0.64mm_HandSolder | 2 | 10K | 24 | 24 | 1 | 10 | Mouser | X
 | 32 | SW1 | SW_PTS636_CNK | 1 | PTS636 SM50J SMTR LFS | 12 | 12 | 1 | 5 | DigiKey | X
 | 33 | U5 | QFN50P700X700X60-49N_STM32 | 1 | STM32G431CBU6 | 6 | 12 | 0.5 | 5 | Mouser | X
 | 34 | R36 | R_0402_1005Metric_Pad0.72x0.64mm_HandSolder | 1 | 4.7K | 12 | 12 | 1 | 5 | Mouser | X
 | 35 | TCAN1051HGVDR1 | SOIC127P600X175-8N_CAN | 1 | ~ | 10 | 12 | 0.83333333333333337 | 5 | MooMoo bought it | X
 | 36 | VR1 | Trimmer_Potentiometer | 1 | 10k | 10 | 12 | 0.83333333333333337 | 5 | MooMoo bought it | X
 | 37 | C5 | C_0603_1608Metric_Pad1.08x0.95mm_HandSolder | 1 | 10uF/35V | 12 | 12 | 1 | 5 | Mouser | X
 | 38 | C2,C1 | C_0402_1005Metric_Pad0.74x0.62mm_HandSolder | 2 | 10uF | 24 | 24 | 1 | 10 | Mouser | X
 | 39 | R32 | R_0402_1005Metric_Pad0.72x0.64mm_HandSolder | 1 | 18K | 12 | 12 | 1 | 5 | Mouser | X
 | 40 | C15 | C_0603_1608Metric_Pad1.08x0.95mm_HandSolder | 1 | 100pF | 12 | 12 | 1 | 5 | Mouser | X
 | 41 | U3 | Soldering Pad for BLDC motor | 1 | Solder Pad | 12 | 12 | 1 | 5 | Mouser | X
 | 42 | Y1 | CSTNE8M00G55Z000R0_Resonator | 1 | 8MHz | 12 | 12 | 1 | 5 | MooMoo bought it | X
 | 43 | R7 | R_0603_1608Metric_Pad0.98x0.95mm_HandSolder | 1 | 1M | 12 | 12 | 1 | 5 | Mouser | X
 | 44 | R6 | R_0402_1005Metric_Pad0.72x0.64mm_HandSolder | 1 | 14K | 12 | 12 | 1 | 5 | Mouser | X
 | 45 | AS5600 | AS5600 | 1 | ~ | 10 | 12 | 0.83333333333333337 | 5 | MooMoo bought it | X
 |  |  |  |  |  | Total Percentage Bought |  | 0.93611111111111123
